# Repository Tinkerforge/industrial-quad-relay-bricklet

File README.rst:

Industrial Quad Relay Bricklet
==============================

This repository contains the firmware source code and the hardware design
files. The documentation generator configs can be found at
https://github.com/Tinkerforge/generators

Repository Content
------------------

software/:
 * examples/: Examples for all supported languages
 * build/: Compiled files
 * src/: Source code of firmware
 * Makefile: Makefile to build project

hardware/:
 * Contains KiCad project files and additionally schematics as PDF

datasheets/:
 * Contains datasheets for sensors and complex ICs that are used

Hardware
--------

The hardware is designed with the open source EDA Suite KiCad
(http://www.kicad.org). Before you are able to open the files,
you have to install the Tinkerforge kicad-libraries
(https://github.com/Tinkerforge/kicad-libraries). You can either clone
them directly in hardware/ or clone them in a separate folder and
symlink them into hardware/
(ln -s kicad_path/kicad-libraries project_path/hardware). After that you
can open the .pro file in hardware/ with KiCad and from there view and
modify the schematics and the PCB layout.

Software
--------

If you want to do your own Brick/Bricklet firmware development we highly
recommend that you use our build environment setup script and read the
tutorial (https://www.tinkerforge.com/en/doc/Tutorials/Tutorial_Build_Environment/Tutorial.html).

To compile the C code we recommend you to install the newest GNU Arm Embedded
Toolchain (https://launchpad.net/gcc-arm-embedded/+download).
You also need to install bricklib (https://github.com/Tinkerforge/bricklib)
and brickletlib (https://github.com/Tinkerforge/brickletlib).

You can either clone it directly in software/src/ or clone it in a
separate folder and symlink it into software/src/
(ln -s bricklib_path/bricklib project_path/software/src/ and
ln -s brickletlib_path/brickletlib project_path/software/src/).
Finally make sure to have CMake installed
(http://www.cmake.org/cmake/resources/software.html).

After that you can build the firmware by invoking make in software/.
The firmware (.bin) can then be found in software/build/ and uploaded
with brickv (click button "Flashing" on start screen).

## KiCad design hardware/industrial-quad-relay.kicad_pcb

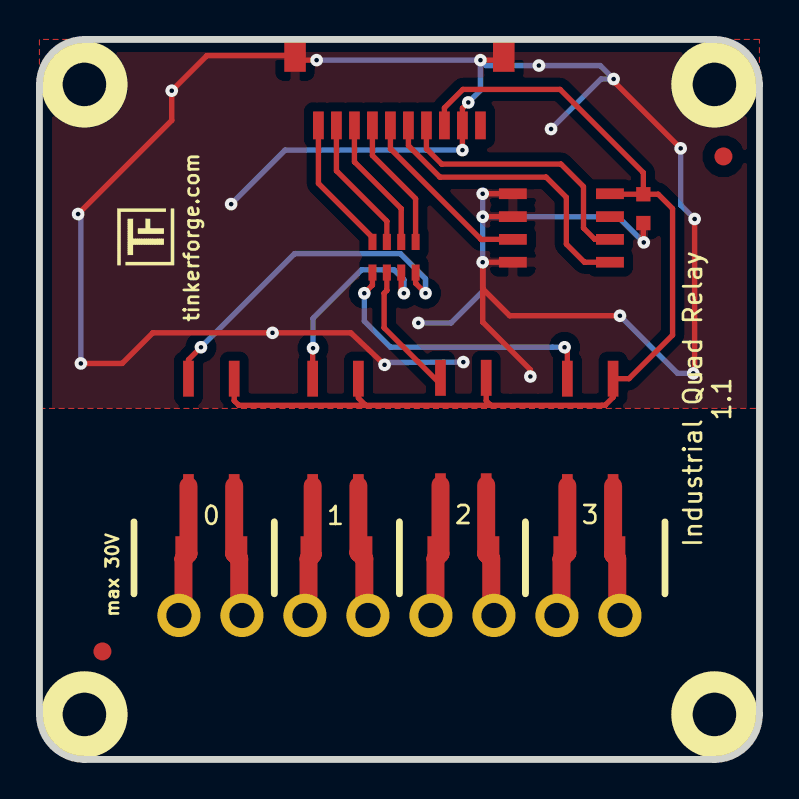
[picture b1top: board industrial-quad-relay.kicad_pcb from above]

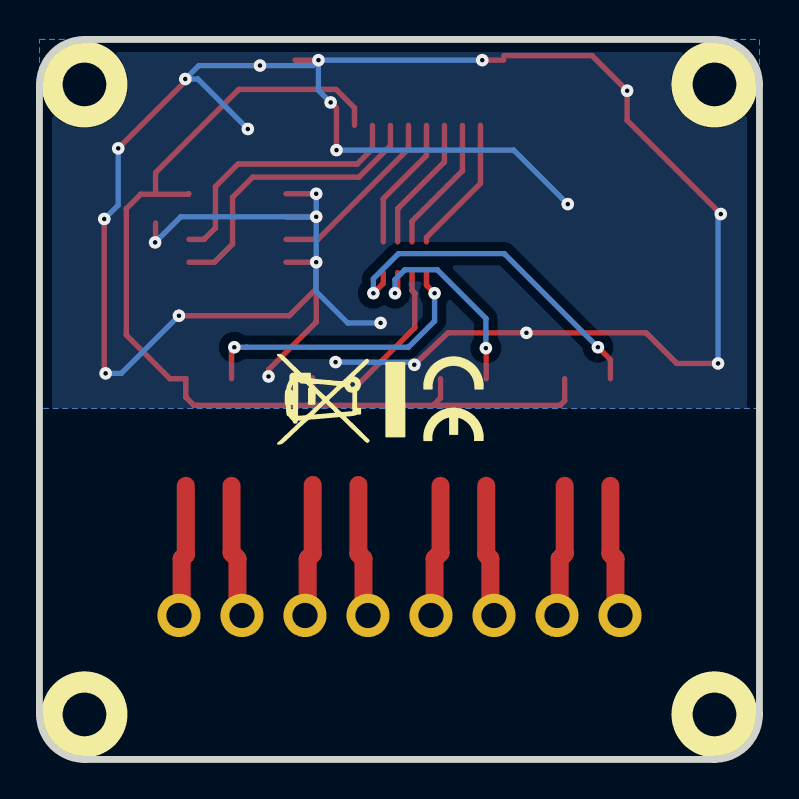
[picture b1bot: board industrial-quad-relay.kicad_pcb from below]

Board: 2 copper layers, 40.0 x 40.0 mm, 21 parts (2 on the bottom side), 21 nets.

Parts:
C1: 100nF; C0603
Fiducial_Mark: VAL**; Fiducial_Mark
Fiducial_Mark#2: VAL**; Fiducial_Mark
P1: CON-SENSOR
P2: Digital Output; OQ_8P
R1, R2, R3, R4: VJ13PC0300KBA; R1210
RP1: 1k; 0603X4
U1: M24C64; SOIC8
U2, U3, U4, U5: CPC1020N; SOP4-WIDE
U6, U7, U8, U9: DRILL; DRILL_NP
VAL: CE_5mm
VAL#2: WEEE_7mm

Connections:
3V3: C1.1, P1.3, U1.8, U2.1, U3.1, U4.1, U5.1
GND: C1.2, P1.2, P1.EP, U1.1, U1.2, U1.4
unnamed: P1.4, U1.6
unnamed: P1.5, U1.5
unnamed: P1.6, U1.3
unnamed: P2.1, R1.1, U2.3
unnamed: P2.2, R1.2, U2.4
unnamed: P2.3, R2.1, U3.3
unnamed: P2.4, R2.2, U3.4
unnamed: P2.5, R3.1, U4.3
unnamed: P2.6, R3.2, U4.4
unnamed: P2.7, R4.1, U5.3
unnamed: P2.8, R4.2, U5.4
unnamed: RP1.5, U5.2
unnamed: RP1.6, U4.2
unnamed: RP1.7, U3.2
unnamed: RP1.8, U2.2
OUTPUT1: P1.7, RP1.1
OUTPUT2: P1.8, RP1.2
OUTPUT3: P1.9, RP1.3
OUTPUT4: P1.10, RP1.4

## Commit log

2012-09-21 Initial Quad Relay commit
2012-09-21 Fix changelog and readme and remove symlinks
2012-09-24 Test for NULL and use uint16 for value instead of uint8
2012-10-24 Make cmake find the correct objcopy binary
    On some systems cmake uses the wrong objcopy binary, tell it to use
    the correct one.
2012-11-13 Support for protocol 2.0
2012-11-23 Add Examples for c, csharp, delphi, java, php, python and ruby
2012-11-23 php: Fix indentation
2012-11-28 Industrial Quad Relay hardware files added
2012-11-28 Add checks for unused pins and fix inverted values
2012-11-28 Fix parameter order in com_return_error calls
    Fix error handling in set_group.
2012-11-29 Make examples compatible to Protocol V2.0
2012-11-29 Make Ruby examples Protocol 2.0 compatible
2012-11-29 Make C examples Protocol 2.0 compatible
2012-11-29 Make Java examples Protocol 2.0 compatible
2012-11-29 Make PHP examples Protocol 2.0 compatible
2012-11-29 Make Delphi/Pascal examples Protocol 2.0 compatible
2012-11-30 delphi: Remove unnecessary parentheses and call destructor again
2012-12-05 Add protocol 2.0 compatability to C# bindings
2013-01-14 Add possibility to set selected values to API
2013-02-07 Use IPconnection disconnect explicitly in examples
2013-02-18 Add Visual Basic .NET example
2013-07-17 Break long lines
2013-08-12 Add shell example
2013-08-12 shell: Explain magic values
2013-08-21 windows: Don't trigger a build in generate_makefile.bat
    Also use normal make instead of a special named one.
2014-01-10 Add Perl examples
2014-01-15 php: Use const for constant values
2014-02-07 Add Mathematica examples
2014-02-10 perl: fixed namespace
2014-02-11 javascript: adding examples
2014-02-11 javascript: short examples
2014-02-18 javascript: examples fixed
2014-02-20 javascript: add html examples
2014-02-24 javascript: port 4280, startExample()
2014-02-28 javascript: Break long lines and cleanup whitespace
2014-03-05 Add LabVIEW example
2014-03-06 labview: Add example in LV2010 format
2014-03-27 matlab: add examples
2014-04-02 java: Unify constants style
2014-04-02 perl: Unify print style
2014-04-17 matlab: Remove \n prefix from input line
2014-04-17 matlab: Add parentheses to make pygments happy
2014-07-15 java: Replace System.console() usage with an Eclipse compatible pattern
2014-12-02 Use ReadLine instead of ReadKey for C# example
2015-02-13 vbnet: Use ReadLine instead of ReadKey
    Because ReadKey doesn't work with a pipe as stdin on the RED Brick.
2015-03-02 windows: Stop cmake from searching for mingw32-make.exe
    Using MinGW Makefiles as generator makes cmake search for mingw32-make.exe
    which might not be installed because GnuWin32's make.exe is used instead.
2015-03-26 update hardware files
2015-04-09 c: Whitespace
2015-06-11 Add CPC1020N datasheet
2015-07-23 Make JavaScript browser example textarea readonly
2015-07-27 Cleanup C/C++, C#, Java, Python and Ruby examplesCleanup C/C++, C# and Java examples
2015-07-29 Reformat changelog
2015-08-07 Use full device class name in Python example
2015-08-12 Fix minor warnings in C/C++ examples
2015-08-14 Cleanup Delphi example
2015-08-18 Unify example loop logic
2015-08-19 Cleanup Perl example
2015-09-09 Remove possible compile warning from example
2015-09-09 Duplicate cmake call to fix bug during cmake creation
2015-10-08 Generator based example cleanup
2015-11-12 matlab: Fix callback handling for R2014a
    http://undocumentedmatlab.com/blog/matlab-callbacks-for-java-events-in-r2014a
2015-11-25 Include date and commit into changelog
2016-05-18 c: Add missing device destroy call
2016-06-29 Whitespace
2016-07-01 Make the change UID comment more explicit
2017-06-02 octave: Use javaObject instead of deprecated java_new
2017-07-31 Add 3d information (final)
2017-07-31 Add 3d model (*.step & *.FCStd)
2017-12-07 mathematica: Also generate .nb files
2018-01-26 c: Fine-tune define placement
2018-02-19 javascript: Close div tag correctly
2018-02-20 Cleanup KiCad libraries config
    Ensure LibDir=kicad-libraries and LibName1=tinkerforge.
    Remove special library.
2018-05-24 perl: Use strict in examples
2018-07-11 Add Makefile with docker support
2018-07-11 Update directory structure and build instructions
2018-07-11 Remove obsolete generate_makefile scripts
2018-11-06 Add rust examples
2018-11-07 rust: Accept host names for ip connection, fix naming inconsistencies
2018-12-14 Add go examples.
2018-12-18 go: Change import path.
2018-12-18 go: Change import path again.
2018-12-20 rust: Reformat examples.
2019-01-24 mqtt: Add examples.
2019-01-24 mqtt: Fix example header.
2019-01-24 mqtt: Remove executable bit in example permissions.
2019-01-24 go: Minor example fixes.
2019-01-24 mqtt: Minor example fixes.
2019-01-29 rust: Fix unused loop index.
2020-01-13 examples: Use python3 input instead of python2 raw_input.
2020-01-13 examples: mqtt: Remove trailing whitespace.
2020-03-23 mqtt: Update for loop style
2020-04-07 examples: rust: Always block when calling bindings functions.
2021-10-25 Update KiCad link
    https://www.kicad.org/blog/2021/10/Avoid-links-to-former-kicad-domain/
2022-07-06 Add license files.

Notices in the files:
hardware/industrial-quad-relay.kicad_pcb:
Licensed under CERN OHL v.1.1
Copyright (©) 2013, B.Nordmeyer
Copyright Tinkerforge GmbH 2013.
This documentation describes Open Hardware and is licensed under the
CERN OHL v. 1.1.
